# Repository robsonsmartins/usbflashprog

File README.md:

# USB Flash/EPROM Programmer
A memory device programmer (Flash/EPROM/E2PROM) board and software, connected to PC by USB port.

[![Latest Tag][tag-shield]][tag-url] [![Latest Commit][commit-shield]][commit-url] [![Forks][forks-shield]][forks-url] [![Stargazers][stars-shield]][stars-url] [![Open Issues][issues-shield]][issues-url] [![License][license-shield]][license-url] [![Project Site][site-shield]][site-url]

[![Build Firmware][build-firmware-shield]][build-firmware-url]
[![Build Software][build-software-shield]][build-software-url]
[![Test Software][test-software-shield]][test-software-url]
[![Test Firmware][test-firmware-shield]][test-firmware-url]
[![CodeQL][codeql-shield]][codeql-url]

## Contents

* [About the Project](#about-the-project)
* [Current Status](#current-status)
* [Releases](#releases)
* [Downloads](#downloads)
* [Operating Systems](#operating-systems)
* [Documentation](#documentation)
* [Hardware Design](#hardware-design)
* [Firmware Project](#firmware-project)
* [Software Project](#software-project)
* [Contributing](#contributing)
* [License](#license)
* [Contact](#contact)
* [Reference](#reference)

## About The Project

The purpose of this board is to allow the programming, reading and verification of writable/rewritable memory devices, such as EPROM, EEPROM, Flash, SRAM, NVRAM – those with parallel bus as well as serial ones (I2C, SPI, Microwire, LPC).

In a future release, programming of some microcontroller families (eg. Microchip PIC, or 8051) may also be supported, via firmware and software upgrade.

## Current Status

The current status of this project is:

-almost%20stable-yellowgreen?style=plastic)
-almost%20stable-yellowgreen?style=plastic)

## Releases

The releases of this project are here: [Releases of the USB Flash/EPROM Programmer](https://github.com/robsonsmartins/usbflashprog/releases).

## Downloads

Downloads of the latest version of the project are available here:

*USB Flash/EPROM Programmer 0.3*:

* [Specifications](https://github.com/robsonsmartins/usbflashprog/releases/download/v0.3.0/specs.pdf) (PDF format, ~2,51MB)
* [Schematics](https://github.com/robsonsmartins/usbflashprog/releases/download/v0.3.0/usbflashprog_sch.pdf) (PDF format, ~148KB)
* [Bill of Materials](https://github.com/robsonsmartins/usbflashprog/releases/download/v0.3.0/usbflashprog_bom.pdf) (PDF format, ~52KB)
* [Firmware Binary (UF2 to Raspberry Pi Pico)](https://github.com/robsonsmartins/usbflashprog/releases/download/v0.3.0/ufprog-uf2-firmware.zip) (ZIP format, ~215KB)
* [Software Installer - Microsoft Windows© 64 bits](https://github.com/robsonsmartins/usbflashprog/releases/download/v0.3.0/ufprog-win64-installer.zip) (ZIP format, ~10MB)
* [Software Installer - Microsoft Windows© 32 bits](https://github.com/robsonsmartins/usbflashprog/releases/download/v0.3.0/ufprog-win32-installer.zip) (ZIP format, ~10MB)
* [Software Installer - Apple macOS© 64 bits](https://github.com/robsonsmartins/usbflashprog/releases/download/v0.3.0/ufprog-macos-installer.zip) (ZIP format, ~21MB)
* [Software Installer - GNU/Linux 64 bits](https://github.com/robsonsmartins/usbflashprog/releases/download/v0.3.0/ufprog-linux64-packages.zip) (ZIP format, ~647KB)
* [Software Installer - FreeBSD 64 bits](https://github.com/robsonsmartins/usbflashprog/releases/download/v0.3.0/ufprog-freebsd_amd64-package.zip) (ZIP format, ~241KB)

## Operating Systems

The USB Flash/EPROM Programmer has compiled installation packages for the following Operating Systems:

### Microsoft Windows©

* Windows 7, or above (32 or 64 bits)

### GNU/Linux

* Ubuntu Linux 20.04, or above (64 bits)
* RedHat/CentOS 8, or above (64 bits)

### Apple macOS©

* macOS 10.13, or above (Intel)

### FreeBSD

* FreeBSD 13.2, or above (64 bits)

## Documentation

The most up-to-date project documentation can be accessed here: [Documentation of the USB Flash/EPROM Programmer](https://robsonsmartins.github.io/usbflashprog/).

## Hardware Design

The most up-to-date hardware design can be accessed here: [Hardware design of the USB Flash/EPROM Programmer](https://github.com/robsonsmartins/usbflashprog/blob/main/hardware/).

## Firmware Project

The most up-to-date firmware project can be accessed here: [Firmware Project of the USB Flash/EPROM Programmer](https://github.com/robsonsmartins/usbflashprog/blob/main/firmware/).

Instructions on how to build the firmware are described in following document: [Firmware Build Instructions](https://github.com/robsonsmartins/usbflashprog/blob/main/firmware/BUILD.md).

## Software Project

The most up-to-date software project can be accessed here: [Software Project of the USB Flash/EPROM Programmer](https://github.com/robsonsmartins/usbflashprog/blob/main/software/).

Instructions on how to build the software are described in following document: [Software Build Instructions](https://github.com/robsonsmartins/usbflashprog/blob/main/software/BUILD.md).

## Contributing

Please read [CONTRIBUTING](https://github.com/robsonsmartins/usbflashprog/blob/main/CONTRIBUTING.md) for more information.

## License

Distributed under the [Creative Commons Attribution-NonCommercial-ShareAlike 4.0 International License][cc-by-nc-sa]. 

See [LICENSE](https://github.com/robsonsmartins/usbflashprog/blob/main/LICENSE) file for more information.

Some components used in this project are available under other licenses. Check each license file distributed with third-party components.

Some brands mentioned are registered and are the property of the respective deteiners/manufacturers.

The same "Terms and Conditions" and "Privacy Policy" of the [Robson Martins Home Page](https://www.robsonmartins.com) apply here:

- [Terms and Conditions](https://www.robsonmartins.com/content/policy/terms.php)
- [Privacy Policy](https://www.robsonmartins.com/content/policy/privacy.php)

## Contact

[![Home Page][contact-site-shield]][contact-site-url] [![LinkedIn][contact-linkedin-shield]][contact-linkedin-url]

## Reference
* [EzoFlash+](http://www.ezoflash.com/) - Parallel Port EPROM/Flash Programmer.
* [MPSP](https://mpsp.robsonmartins.com) - Microchip&copy; PIC Serial Port Programmer.
* [PK2C](https://pk2c.robsonmartins.com) - Microchip&copy; PIC Kit 2 Clone Programmer.

---

This work is licensed under a [Creative Commons Attribution-NonCommercial-ShareAlike 4.0 International License][cc-by-nc-sa].

[![CC BY-NC-SA 4.0][cc-by-nc-sa-image]][cc-by-nc-sa]

[cc-by-nc-sa]: http://creativecommons.org/licenses/by-nc-sa/4.0/
[cc-by-nc-sa-image]: https://licensebuttons.net/l/by-nc-sa/4.0/88x31.png

[tag-shield]: https://img.shields.io/github/v/tag/robsonsmartins/usbflashprog?style=plastic
[tag-url]: https://github.com/robsonsmartins/usbflashprog/tags
[commit-shield]: https://img.shields.io/github/last-commit/robsonsmartins/usbflashprog?style=plastic
[commit-url]: https://github.com/robsonsmartins/usbflashprog/graphs/commit-activity
[forks-shield]: https://img.shields.io/github/forks/robsonsmartins/usbflashprog?style=plastic
[forks-url]: https://github.com/robsonsmartins/usbflashprog/network/members
[stars-shield]: https://img.shields.io/github/stars/robsonsmartins/usbflashprog?style=plastic
[stars-url]: https://github.com/robsonsmartins/usbflashprog/stargazers
[issues-shield]: https://img.shields.io/github/issues/robsonsmartins/usbflashprog?style=plastic
[issues-url]: https://github.com/robsonsmartins/usbflashprog/issues
[license-shield]: https://img.shields.io/badge/License-CC%20BY--NC--SA%204.0-lightgrey.svg?style=plastic
[license-url]: https://github.com/robsonsmartins/usbflashprog/blob/master/LICENSE
[site-shield]: https://img.shields.io/badge/project%20site-usbflashprog-orange?style=plastic
[site-url]: https://usbflashprog.robsonmartins.com

[build-firmware-shield]: https://github.com/robsonsmartins/usbflashprog/actions/workflows/firmware.yml/badge.svg?style=plastic
[build-firmware-url]: https://github.com/robsonsmartins/usbflashprog/actions/workflows/firmware.yml
[build-software-shield]: https://github.com/robsonsmartins/usbflashprog/actions/workflows/software.yml/badge.svg?style=plastic
[build-software-url]: https://github.com/robsonsmartins/usbflashprog/actions/workflows/software.yml
[test-firmware-shield]: https://github.com/robsonsmartins/usbflashprog/actions/workflows/test-firmware.yml/badge.svg?style=plastic
[test-firmware-url]: https://github.com/robsonsmartins/usbflashprog/actions/workflows/test-firmware.yml
[test-software-shield]: https://github.com/robsonsmartins/usbflashprog/actions/workflows/test-software.yml/badge.svg?style=plastic
[test-software-url]: https://github.com/robsonsmartins/usbflashprog/actions/workflows/test-software.yml
[codeql-shield]: https://github.com/robsonsmartins/usbflashprog/actions/workflows/codeql-analysis.yml/badge.svg?style=plastic
[codeql-url]:https://github.com/robsonsmartins/usbflashprog/actions/workflows/codeql-analysis.yml

[contact-site-shield]: https://img.shields.io/badge/Home%20Page-robsonmartins.com-green?style=plastic
[contact-site-url]: https://www.robsonmartins.com
[contact-linkedin-shield]: https://img.shields.io/badge/LinkedIn-robsonmartins-blue?style=plastic
[contact-linkedin-url]: https://www.linkedin.com/in/robsonmartins/

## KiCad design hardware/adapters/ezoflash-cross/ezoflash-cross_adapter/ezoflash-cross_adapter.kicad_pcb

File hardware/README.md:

# USB Flash/EPROM Programmer

A memory device programmer (Flash/EPROM/E2PROM) board and software, connected to PC by USB port.

## Hardware Design

### Schematic Diagram

The most up-to-date schematic diagram can be accessed here: [Schematic diagram of the USB Flash/EPROM Programmer](https://robsonsmartins.github.io/usbflashprog/hardware/usbflashprog_sch.pdf).

### Bill of Materials (BOM)

The most up-to-date BOM can be accessed here: [Bill of Materials of the USB Flash/EPROM Programmer](https://robsonsmartins.github.io/usbflashprog/hardware/usbflashprog_bom.pdf).

## Software versions

The following CAD software (opensource and multiplatform) was used to draw the schematic diagram and PCB:

- [Kicad](https://www.kicad.org), version 7.0.5.

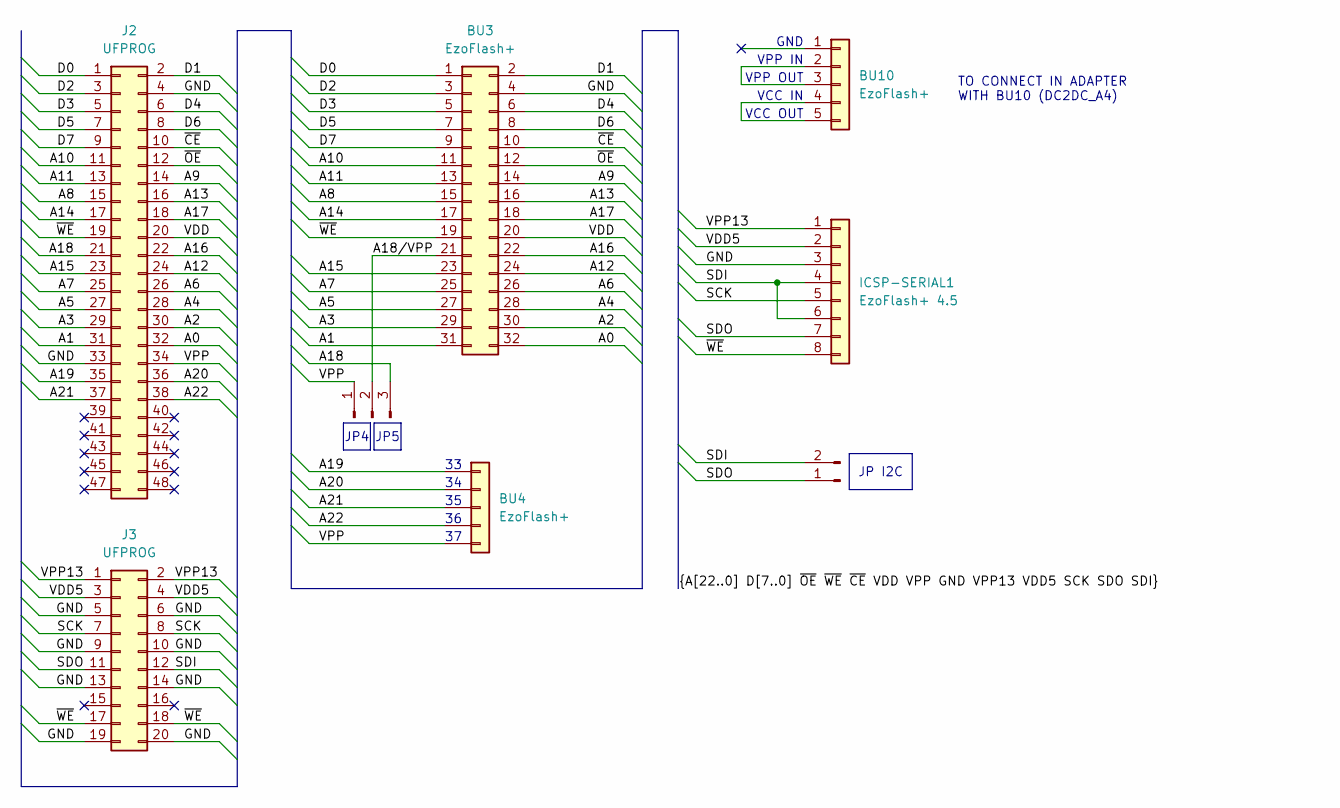
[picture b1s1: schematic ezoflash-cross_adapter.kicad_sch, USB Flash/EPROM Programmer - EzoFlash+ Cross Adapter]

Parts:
BU3: EzoFlash+; PinSocket_2x16_P2.54mm_Vertical
BU4: EzoFlash+; PinSocket_1x05_P2.54mm_Vertical
BU10: EzoFlash+; PinHeader_1x05_P2.54mm_Vertical
ICSP-SERIAL1: EzoFlash+ 4.5; PinHeader_1x08_P2.54mm_Vertical
J2: UFPROG; PinHeader_2x24_P2.54mm_Vertical
J3: UFPROG; PinHeader_2x10_P2.54mm_Vertical
JP4JP5: Conn_01x03_Pin; PinHeader_1x03_P2.54mm_Vertical
JPI2C1: Conn_01x02_Pin; PinHeader_1x02_P2.54mm_Vertical

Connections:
/A0: BU3.32, J2.32
/A1: BU3.31, J2.31
/A2: BU3.30, J2.30
/A3: BU3.29, J2.29
/A4: BU3.28, J2.28
/A5: BU3.27, J2.27
/A6: BU3.26, J2.26
/A7: BU3.25, J2.25
/A8: BU3.15, J2.15
/A9: BU3.14, J2.14
/A10: BU3.11, J2.11
/A11: BU3.13, J2.13
/A12: BU3.24, J2.24
/A13: BU3.16, J2.16
/A14: BU3.17, J2.17
/A15: BU3.23, J2.23
/A16: BU3.22, J2.22
/A17: BU3.18, J2.18
/A18: J2.21, JP4JP5.3
/A18/VPP: BU3.21, JP4JP5.2
/A19: BU4.1, J2.35
/A20: BU4.2, J2.36
/A21: BU4.3, J2.37
/A22: BU4.4, J2.38
/D0: BU3.1, J2.1
/D1: BU3.2, J2.2
/D2: BU3.3, J2.3
/D3: BU3.5, J2.5
/D4: BU3.6, J2.6
/D5: BU3.7, J2.7
/D6: BU3.8, J2.8
/D7: BU3.9, J2.9
/GND: BU3.4, ICSP-SERIAL1.3, J2.4, J2.33, J3.5, J3.6, J3.9, J3.10, J3.13, J3.14, J3.19, J3.20
/SCK: ICSP-SERIAL1.5, J3.7, J3.8
/SDI: ICSP-SERIAL1.4, ICSP-SERIAL1.6, J3.12, JPI2C1.2
/SDO: ICSP-SERIAL1.7, J3.11, JPI2C1.1
/VDD: BU3.20, J2.20
/VDD5: ICSP-SERIAL1.2, J3.3, J3.4
/VPP: BU4.5, J2.34, JP4JP5.1
/VPP13: ICSP-SERIAL1.1, J3.1, J3.2
/~CE: BU3.10, J2.10
/~OE: BU3.12, J2.12
/~WE: BU3.19, ICSP-SERIAL1.8, J2.19, J3.17, J3.18
unnamed: BU10.2, BU10.3
unnamed: BU10.4, BU10.5

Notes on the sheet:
JP I2C
JP4
JP5
VPP IN
VCC OUT
VPP OUT
VCC IN
TO CONNECT IN ADAPTER WITH BU10 (DC2DC_A4)
GND

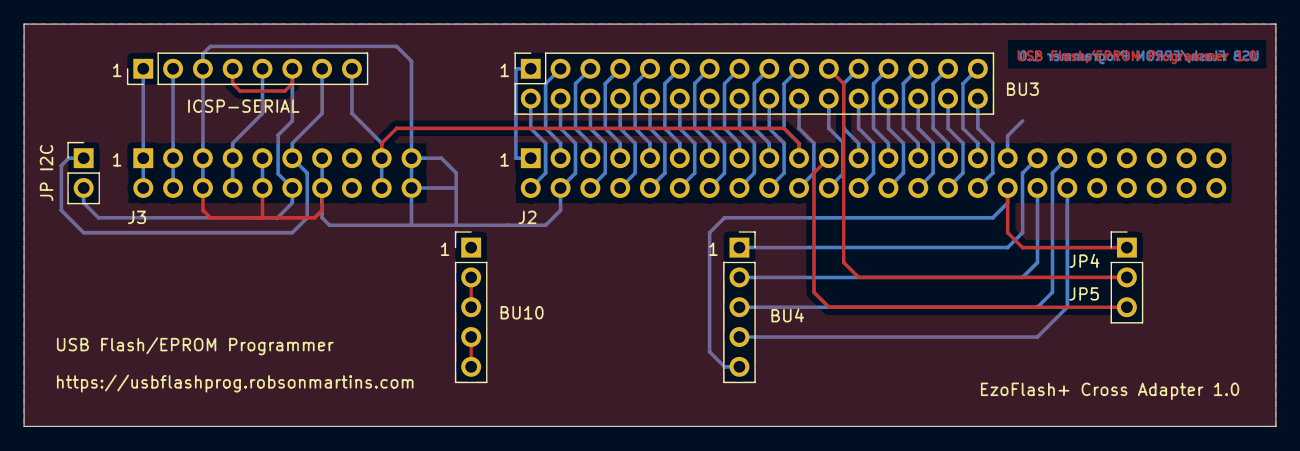
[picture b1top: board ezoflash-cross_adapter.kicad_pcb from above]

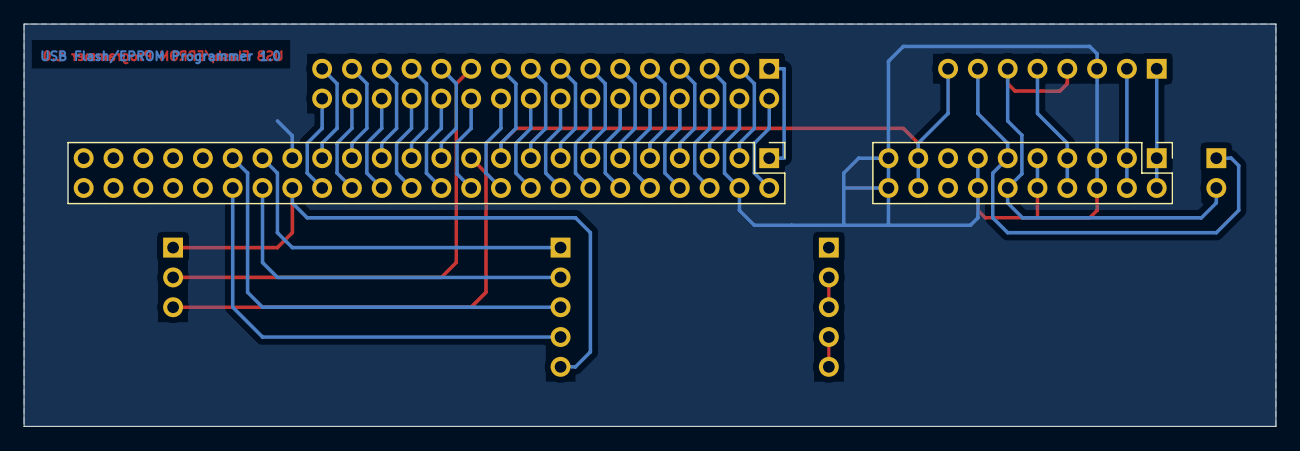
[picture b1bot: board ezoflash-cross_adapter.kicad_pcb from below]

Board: 2 copper layers, 106.7 x 34.3 mm, 8 parts (2 on the bottom side), 45 nets.

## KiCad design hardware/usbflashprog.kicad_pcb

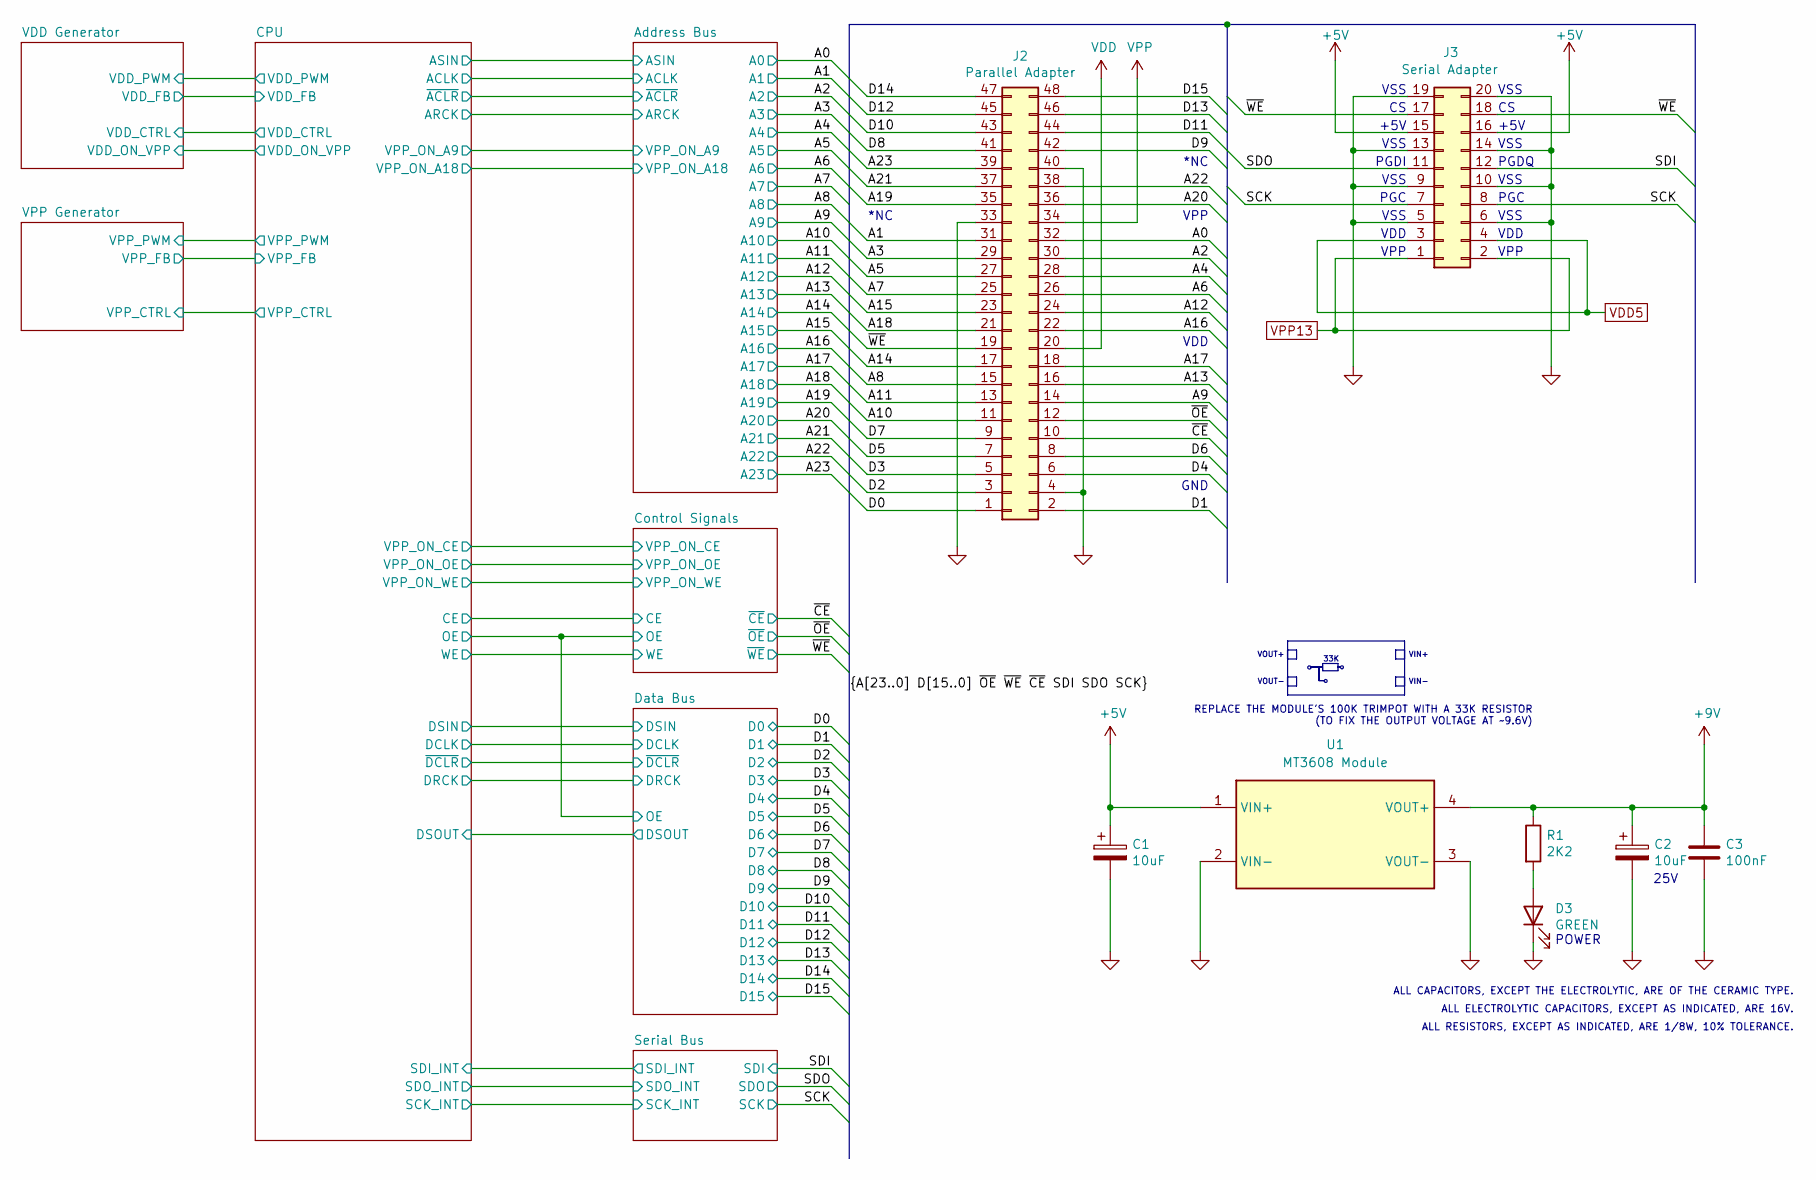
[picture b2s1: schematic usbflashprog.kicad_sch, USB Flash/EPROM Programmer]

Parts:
C1, C2: 10uF; CP_Radial_D5.0mm_P2.50mm
C3: 100nF; C_Disc_D5.0mm_W2.5mm_P5.00mm
D3: GREEN; LED_D3.0mm
J2: Parallel Adapter; PinSocket_2x24_P2.54mm_Vertical
J3: Serial Adapter; PinSocket_2x10_P2.54mm_Vertical
R1: 2K2; R_Axial_DIN0204_L3.6mm_D1.6mm_P7.62mm_Horizontal
U1: MT3608 Module; MT3608_module

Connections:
+5V: C1.1, J3.15, J3.16, U1.1 (VIN+); also elsewhere on the board
+9V: C2.1, C3.1, R1.1, U1.4 (VOUT+); also elsewhere on the board
/A0: J2.32; also elsewhere on the board
/A1: J2.31; also elsewhere on the board
/A2: J2.30; also elsewhere on the board
/A3: J2.29; also elsewhere on the board
/A4: J2.28; also elsewhere on the board
/A5: J2.27; also elsewhere on the board
/A6: J2.26; also elsewhere on the board
/A7: J2.25; also elsewhere on the board
/A8: J2.15; also elsewhere on the board
/A9: J2.14; also elsewhere on the board
/A10: J2.11; also elsewhere on the board
/A11: J2.13; also elsewhere on the board
/A12: J2.24; also elsewhere on the board
/A13: J2.16; also elsewhere on the board
/A14: J2.17; also elsewhere on the board
/A15: J2.23; also elsewhere on the board
/A16: J2.22; also elsewhere on the board
/A17: J2.18; also elsewhere on the board
/A18: J2.21; also elsewhere on the board
/A19: J2.35; also elsewhere on the board
/A20: J2.36; also elsewhere on the board
/A21: J2.37; also elsewhere on the board
/A22: J2.38; also elsewhere on the board
/A23: J2.39; also elsewhere on the board
/D0: J2.1; also elsewhere on the board
/D1: J2.2; also elsewhere on the board
/D2: J2.3; also elsewhere on the board
/D3: J2.5; also elsewhere on the board
/D4: J2.6; also elsewhere on the board
/D5: J2.7; also elsewhere on the board
/D6: J2.8; also elsewhere on the board
/D7: J2.9; also elsewhere on the board
/D8: J2.41; also elsewhere on the board
/D9: J2.42; also elsewhere on the board
/D10: J2.43; also elsewhere on the board
/D11: J2.44; also elsewhere on the board
/D12: J2.45; also elsewhere on the board
/D13: J2.46; also elsewhere on the board
/D14: J2.47; also elsewhere on the board
/D15: J2.48; also elsewhere on the board
/SCK: J3.7, J3.8; also elsewhere on the board
/SDI: J3.12; also elsewhere on the board
/SDO: J3.11; also elsewhere on the board
/~CE: J2.10; also elsewhere on the board
/~OE: J2.12; also elsewhere on the board
/~WE: J2.19, J3.17, J3.18; also elsewhere on the board
GND: C1.2, C2.2, C3.2, D3.1 (K), J2.4, J2.33, J2.40, J3.5, J3.6, J3.9, J3.10, J3.13, J3.14, J3.19, J3.20, U1.2 (VIN-), U1.3 (VOUT-); also elsewhere on the board
unnamed: D3.2 (A), R1.2
VDD: J2.20; also elsewhere on the board
VDD5: J3.3, J3.4; also elsewhere on the board
VPP: J2.34; also elsewhere on the board
VPP13: J3.1, J3.2; also elsewhere on the board

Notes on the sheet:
+5V
VSS
PGC
VPP
25V
*NC
POWER
VIN-
VDD
ALL CAPACITORS, EXCEPT THE ELECTROLYTIC, ARE OF THE CERAMIC TYPE.
33K
VOUT+
ALL RESISTORS, EXCEPT AS INDICATED, ARE 1/8W, 10% TOLERANCE.
VOUT-
PGDI
PGDQ
REPLACE THE MODULE'S 100K TRIMPOT WITH A 33K RESISTOR (TO FIX THE OUTPUT VOLTAGE AT ~9.6V)
VIN+
GND
ALL ELECTROLYTIC CAPACITORS, EXCEPT AS INDICATED, ARE 16V.

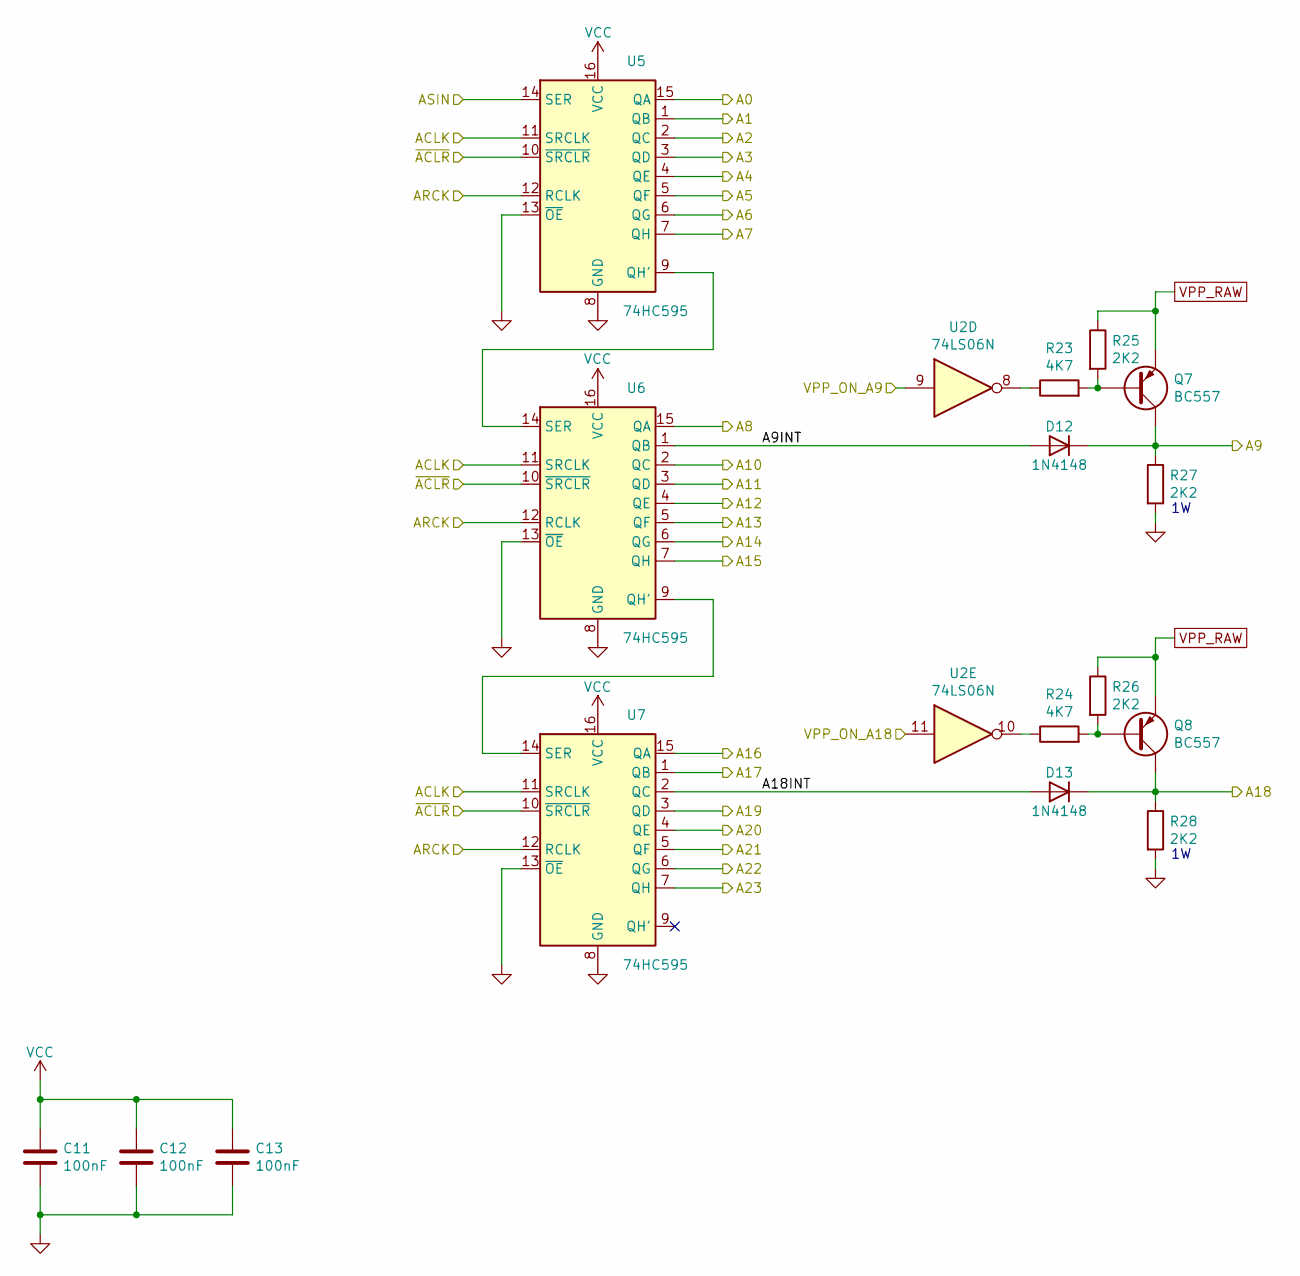
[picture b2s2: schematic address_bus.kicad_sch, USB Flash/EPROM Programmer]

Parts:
C11, C12, C13: 100nF; C_Disc_D5.0mm_W2.5mm_P5.00mm
D12, D13: 1N4148; D_DO-34_SOD68_P7.62mm_Horizontal
Q7, Q8: BC557; TO-92_Inline_Wide
R23, R24: 4K7; R_Axial_DIN0204_L3.6mm_D1.6mm_P7.62mm_Horizontal
R25, R26, R27, R28: 2K2; R_Axial_DIN0204_L3.6mm_D1.6mm_P7.62mm_Horizontal
U2: 74LS06N; DIP-14_W7.62mm
U5, U6, U7: 74HC595; DIP-16_W7.62mm

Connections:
/A0: U5.15 (QA); also elsewhere on the board
/A1: U5.1 (QB); also elsewhere on the board
/A2: U5.2 (QC); also elsewhere on the board
/A3: U5.3 (QD); also elsewhere on the board
/A4: U5.4 (QE); also elsewhere on the board
/A5: U5.5 (QF); also elsewhere on the board
/A6: U5.6 (QG); also elsewhere on the board
/A7: U5.7 (QH); also elsewhere on the board
/A8: U6.15 (QA); also elsewhere on the board
/A9: D12.1 (K), Q7.1 (C), R27.1; also elsewhere on the board
/A10: U6.2 (QC); also elsewhere on the board
/A11: U6.3 (QD); also elsewhere on the board
/A12: U6.4 (QE); also elsewhere on the board
/A13: U6.5 (QF); also elsewhere on the board
/A14: U6.6 (QG); also elsewhere on the board
/A15: U6.7 (QH); also elsewhere on the board
/A16: U7.15 (QA); also elsewhere on the board
/A17: U7.1 (QB); also elsewhere on the board
/A18: D13.1 (K), Q8.1 (C), R28.1; also elsewhere on the board
/A19: U7.3 (QD); also elsewhere on the board
/A20: U7.4 (QE); also elsewhere on the board
/A21: U7.5 (QF); also elsewhere on the board
/A22: U7.6 (QG); also elsewhere on the board
/A23: U7.7 (QH); also elsewhere on the board
/Address Bus/A9INT: D12.2 (A), U6.1 (QB)
/Address Bus/A18INT: D13.2 (A), U7.2 (QC)
/Address Bus/ACLK: U5.11 (SRCLK), U6.11 (SRCLK), U7.11 (SRCLK); also elsewhere on the board
/Address Bus/ARCK: U5.12 (RCLK), U6.12 (RCLK), U7.12 (RCLK); also elsewhere on the board
/Address Bus/ASIN: U5.14 (SER); also elsewhere on the board
/Address Bus/VPP_ON_A9: U2.9; also elsewhere on the board
/Address Bus/VPP_ON_A18: U2.11; also elsewhere on the board
/Address Bus/~ACLR: U5.10 (~SRCLR), U6.10 (~SRCLR), U7.10 (~SRCLR); also elsewhere on the board
GND: C11.2, C12.2, C13.2, R27.2, R28.2, U5.8 (GND), U5.13 (~OE), U6.8 (GND), U6.13 (~OE), U7.8 (GND), U7.13 (~OE); also elsewhere on the board
unnamed: Q7.2 (B), R23.2, R25.2
unnamed: Q8.2 (B), R24.2, R26.2
unnamed: R23.1, U2.8
unnamed: R24.1, U2.10
unnamed: U5.9 (QH'), U6.14 (SER)
unnamed: U6.9 (QH'), U7.14 (SER)
VCC: C11.1, C12.1, C13.1, U5.16 (VCC), U6.16 (VCC), U7.16 (VCC); also elsewhere on the board
VPP_RAW: Q7.3 (E), Q8.3 (E), R25.1, R26.1; also elsewhere on the board

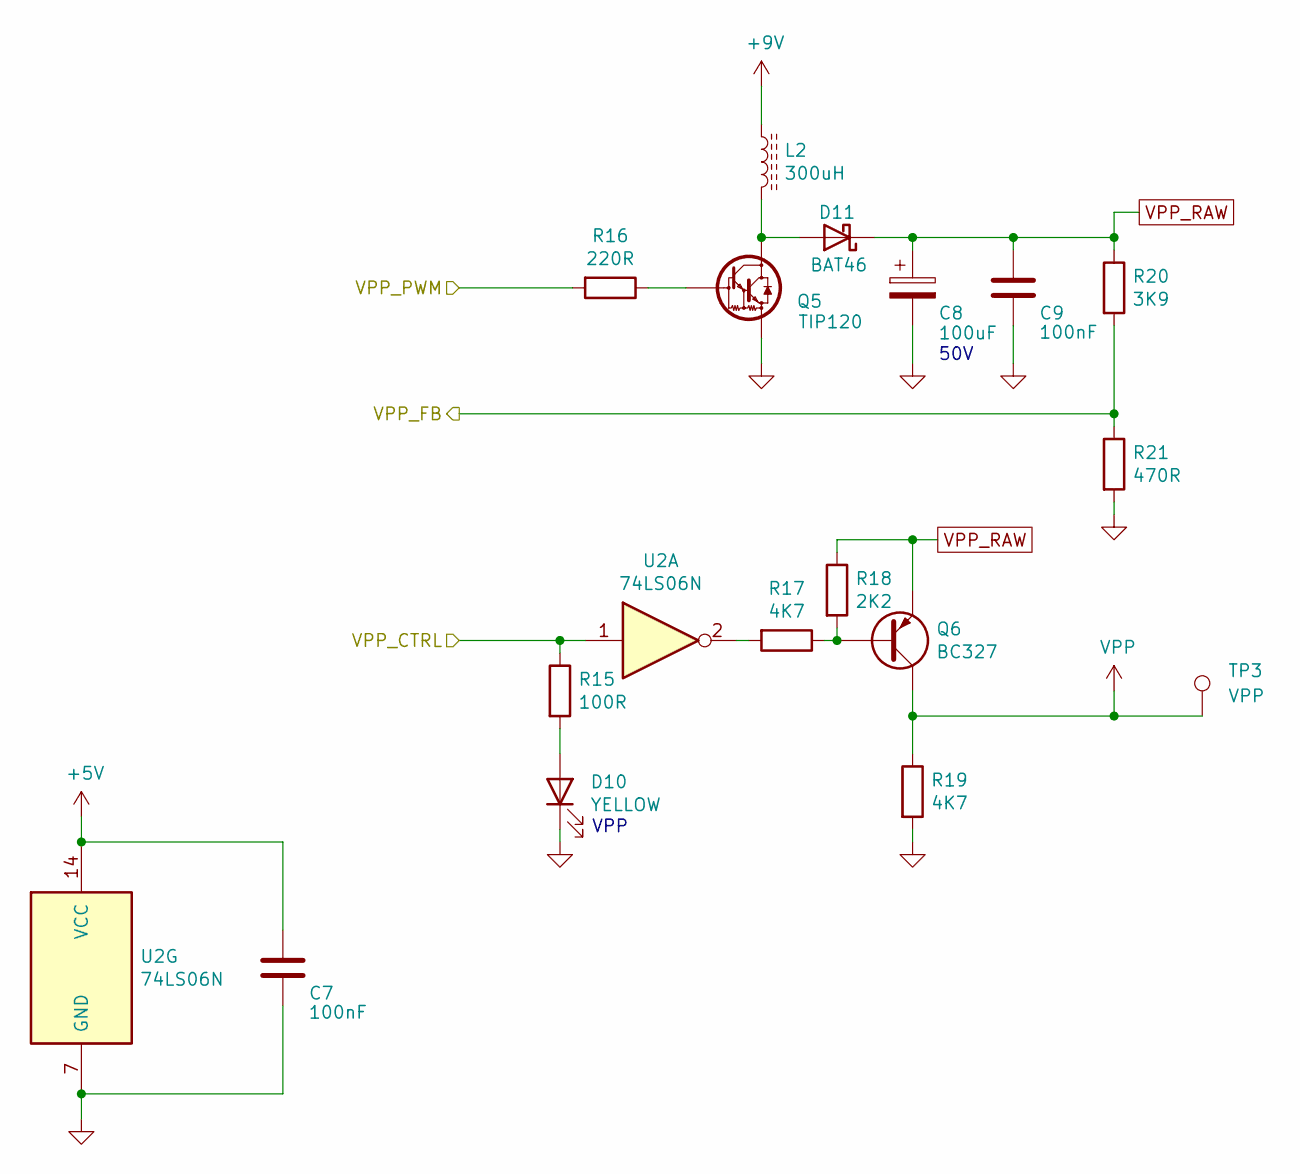
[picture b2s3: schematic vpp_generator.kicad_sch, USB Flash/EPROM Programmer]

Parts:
C7, C9: 100nF; C_Disc_D5.0mm_W2.5mm_P5.00mm
C8: 100uF; CP_Radial_D8.0mm_P3.50mm
D10: YELLOW; LED_D3.0mm
D11: BAT46; D_DO-34_SOD68_P7.62mm_Horizontal
L2: 300uH; L_Toroid_Vertical_L13.0mm_W6.5mm_P5.60mm
Q5: TIP120; TO-220-3_Vertical
Q6: BC327; TO-92_Inline_Wide
R15: 100R; R_Axial_DIN0204_L3.6mm_D1.6mm_P7.62mm_Horizontal
R16: 220R; R_Axial_DIN0204_L3.6mm_D1.6mm_P7.62mm_Horizontal
R17, R19: 4K7; R_Axial_DIN0204_L3.6mm_D1.6mm_P7.62mm_Horizontal
R18: 2K2; R_Axial_DIN0204_L3.6mm_D1.6mm_P7.62mm_Horizontal
R20: 3K9; R_Axial_DIN0204_L3.6mm_D1.6mm_P7.62mm_Horizontal
R21: 470R; R_Axial_DIN0204_L3.6mm_D1.6mm_P7.62mm_Horizontal
TP3: VPP; TestPoint_THTPad_2.5x2.5mm_Drill1.2mm
U2: 74LS06N; DIP-14_W7.62mm

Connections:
+5V: C7.1, U2.14 (VCC); also elsewhere on the board
+9V: L2.1; also elsewhere on the board
/CPU/VPP_CTRL: R15.1, U2.1; also elsewhere on the board
/CPU/VPP_FB: R20.2, R21.1; also elsewhere on the board
/CPU/VPP_PWM: R16.2; also elsewhere on the board
GND: C7.2, C8.2, C9.2, D10.1 (K), Q5.3 (E), R19.2, R21.2, U2.7 (GND); also elsewhere on the board
unnamed: D10.2 (A), R15.2
unnamed: D11.2 (A), L2.2, Q5.2 (C)
unnamed: Q5.1 (B), R16.1
unnamed: Q6.2 (B), R17.1, R18.2
unnamed: R17.2, U2.2
VPP: Q6.1 (C), R19.1, TP3.1; also elsewhere on the board
VPP_RAW: C8.1, C9.1, D11.1 (K), Q6.3 (E), R18.1, R20.1; also elsewhere on the board

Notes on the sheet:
VPP
50V

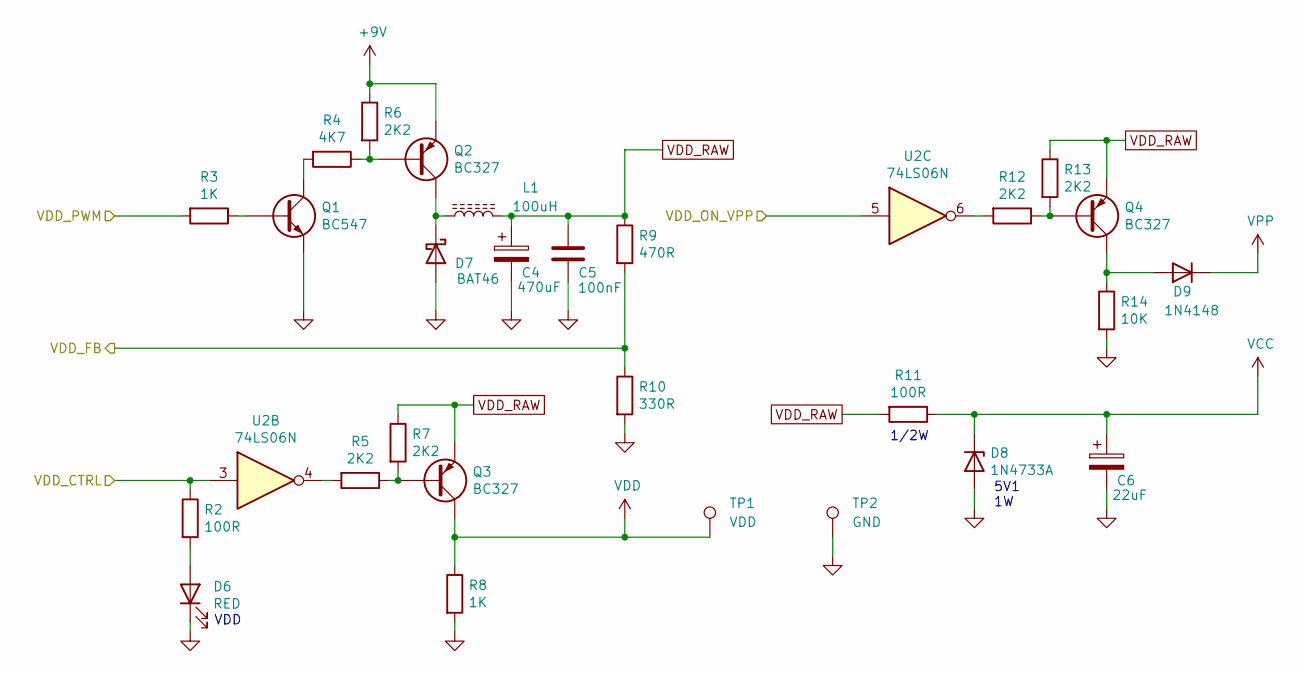
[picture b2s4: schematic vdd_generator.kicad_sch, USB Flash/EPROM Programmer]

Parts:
C4: 470uF; CP_Radial_D8.0mm_P3.80mm
C5: 100nF; C_Disc_D5.0mm_W2.5mm_P5.00mm
C6: 22uF; CP_Radial_D5.0mm_P2.50mm
D6: RED; LED_D3.0mm
D7: BAT46; D_DO-34_SOD68_P7.62mm_Horizontal
D8: 1N4733A; D_DO-35_SOD27_P7.62mm_Horizontal
D9: 1N4148; D_DO-34_SOD68_P7.62mm_Horizontal
L1: 100uH; L_Toroid_Vertical_L13.0mm_W6.5mm_P5.60mm
Q1: BC547; TO-92_Inline_Wide
Q2, Q3, Q4: BC327; TO-92_Inline_Wide
R2, R11: 100R; R_Axial_DIN0204_L3.6mm_D1.6mm_P7.62mm_Horizontal
R3, R8: 1K; R_Axial_DIN0204_L3.6mm_D1.6mm_P7.62mm_Horizontal
R4: 4K7; R_Axial_DIN0204_L3.6mm_D1.6mm_P7.62mm_Horizontal
R5, R6, R7, R12, R13: 2K2; R_Axial_DIN0204_L3.6mm_D1.6mm_P7.62mm_Horizontal
R9: 470R; R_Axial_DIN0204_L3.6mm_D1.6mm_P7.62mm_Horizontal
R10: 330R; R_Axial_DIN0204_L3.6mm_D1.6mm_P7.62mm_Horizontal
R14: 10K; R_Axial_DIN0204_L3.6mm_D1.6mm_P7.62mm_Horizontal
TP1: VDD; TestPoint_THTPad_2.5x2.5mm_Drill1.2mm
TP2: GND; TestPoint_THTPad_2.5x2.5mm_Drill1.2mm
U2: 74LS06N; DIP-14_W7.62mm

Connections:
+9V: Q2.3 (E), R6.1; also elsewhere on the board
/CPU/VDD_CTRL: R2.1, U2.3; also elsewhere on the board
/CPU/VDD_FB: R9.2, R10.1; also elsewhere on the board
/CPU/VDD_ON_VPP: U2.5; also elsewhere on the board
/CPU/VDD_PWM: R3.2; also elsewhere on the board
GND: C4.2, C5.2, C6.2, D6.1 (K), D7.2 (A), D8.2 (A), Q1.3 (E), R8.2, R10.2, R14.2, TP2.1; also elsewhere on the board
unnamed: D6.2 (A), R2.2
unnamed: D7.1 (K), L1.1, Q2.1 (C)
unnamed: D9.2 (A), Q4.1 (C), R14.1
unnamed: Q1.2 (B), R3.1
unnamed: Q1.1 (C), R4.2
unnamed: Q2.2 (B), R4.1, R6.2
unnamed: Q3.2 (B), R5.1, R7.2
unnamed: Q4.2 (B), R12.1, R13.2
unnamed: R5.2, U2.4
unnamed: R12.2, U2.6
VCC: C6.1, D8.1 (K), R11.1; also elsewhere on the board
VDD: Q3.1 (C), R8.1, TP1.1; also elsewhere on the board
VDD_RAW: C4.1, C5.1, L1.2, Q3.3 (E), Q4.3 (E), R7.1, R9.1, R11.2, R13.1; also elsewhere on the board
VPP: D9.1 (K); also elsewhere on the board

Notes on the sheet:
1/2W
5V1 1W
VDD

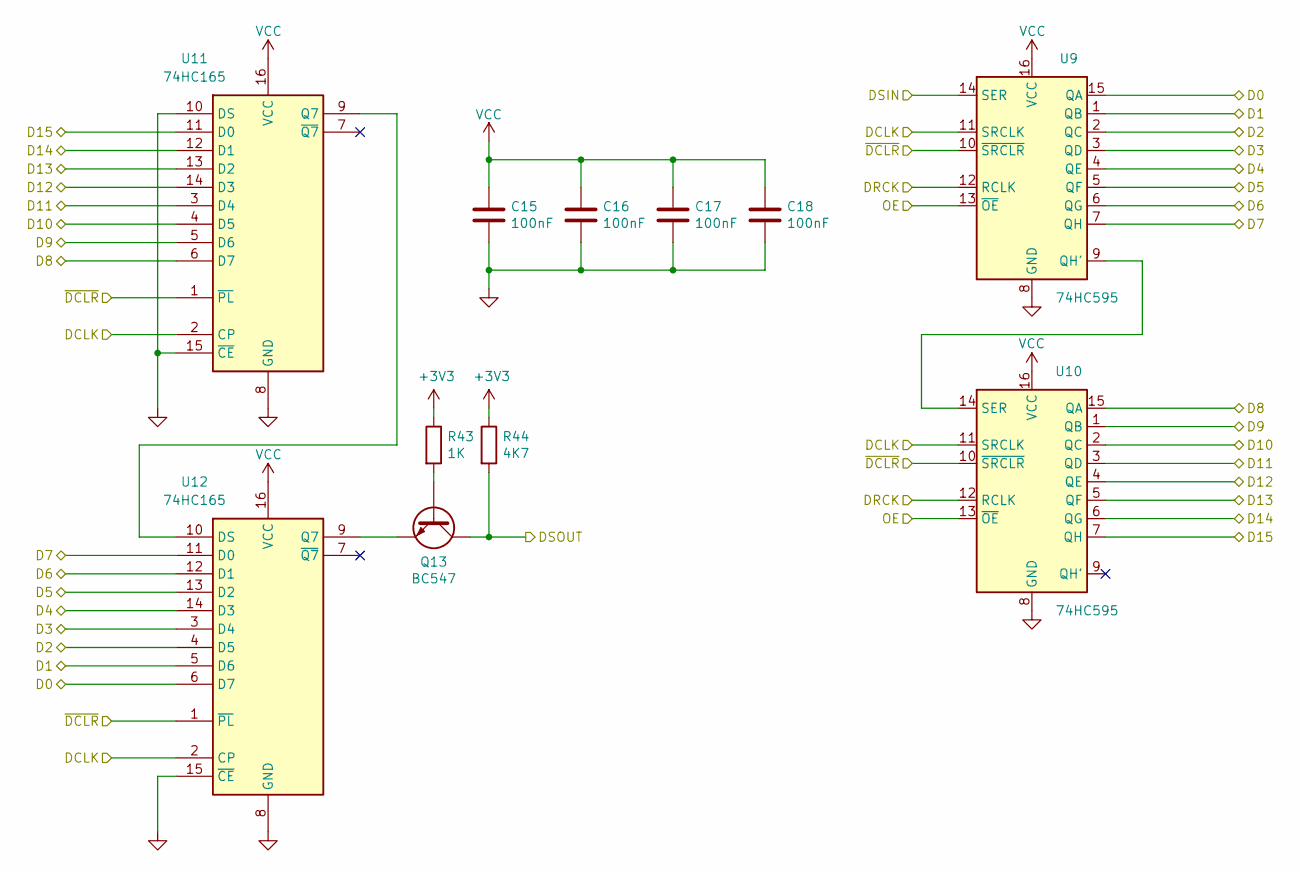
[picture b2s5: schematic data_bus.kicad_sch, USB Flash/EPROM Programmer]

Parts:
C15, C16, C17, C18: 100nF; C_Disc_D5.0mm_W2.5mm_P5.00mm
Q13: BC547; TO-92_Inline_Wide
R43: 1K; R_Axial_DIN0204_L3.6mm_D1.6mm_P7.62mm_Horizontal
R44: 4K7; R_Axial_DIN0204_L3.6mm_D1.6mm_P7.62mm_Horizontal
U9, U10: 74HC595; DIP-16_W7.62mm
U11, U12: 74HC165; DIP-16_W7.62mm

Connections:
+3V3: R43.1, R44.1; also elsewhere on the board
/CPU/DCLK: U9.11 (SRCLK), U10.11 (SRCLK), U11.2 (CP), U12.2 (CP); also elsewhere on the board
/CPU/DRCK: U9.12 (RCLK), U10.12 (RCLK); also elsewhere on the board
/CPU/DSIN: U9.14 (SER); also elsewhere on the board
/CPU/DSOUT: Q13.1 (C), R44.2; also elsewhere on the board
/CPU/OE: U9.13 (~OE), U10.13 (~OE); also elsewhere on the board
/CPU/~DCLR: U9.10 (~SRCLR), U10.10 (~SRCLR), U11.1 (~PL), U12.1 (~PL); also elsewhere on the board
/D0: U9.15 (QA), U12.6 (D7); also elsewhere on the board
/D1: U9.1 (QB), U12.5 (D6); also elsewhere on the board
/D2: U9.2 (QC), U12.4 (D5); also elsewhere on the board
/D3: U9.3 (QD), U12.3 (D4); also elsewhere on the board
/D4: U9.4 (QE), U12.14 (D3); also elsewhere on the board
/D5: U9.5 (QF), U12.13 (D2); also elsewhere on the board
/D6: U9.6 (QG), U12.12 (D1); also elsewhere on the board
/D7: U9.7 (QH), U12.11 (D0); also elsewhere on the board
/D8: U10.15 (QA), U11.6 (D7); also elsewhere on the board
/D9: U10.1 (QB), U11.5 (D6); also elsewhere on the board
/D10: U10.2 (QC), U11.4 (D5); also elsewhere on the board
/D11: U10.3 (QD), U11.3 (D4); also elsewhere on the board
/D12: U10.4 (QE), U11.14 (D3); also elsewhere on the board
/D13: U10.5 (QF), U11.13 (D2); also elsewhere on the board
/D14: U10.6 (QG), U11.12 (D1); also elsewhere on the board
/D15: U10.7 (QH), U11.11 (D0); also elsewhere on the board
GND: C15.2, C16.2, C17.2, C18.2, U9.8 (GND), U10.8 (GND), U11.8 (GND), U11.10 (DS), U11.15 (~CE), U12.8 (GND), U12.15 (~CE); also elsewhere on the board
unnamed: Q13.2 (B), R43.2
unnamed: Q13.3 (E), U12.9 (Q7)
unnamed: U9.9 (QH'), U10.14 (SER)
unnamed: U11.9 (Q7), U12.10 (DS)
VCC: C15.1, C16.1, C17.1, C18.1, U9.16 (VCC), U10.16 (VCC), U11.16 (VCC), U12.16 (VCC); also elsewhere on the board
